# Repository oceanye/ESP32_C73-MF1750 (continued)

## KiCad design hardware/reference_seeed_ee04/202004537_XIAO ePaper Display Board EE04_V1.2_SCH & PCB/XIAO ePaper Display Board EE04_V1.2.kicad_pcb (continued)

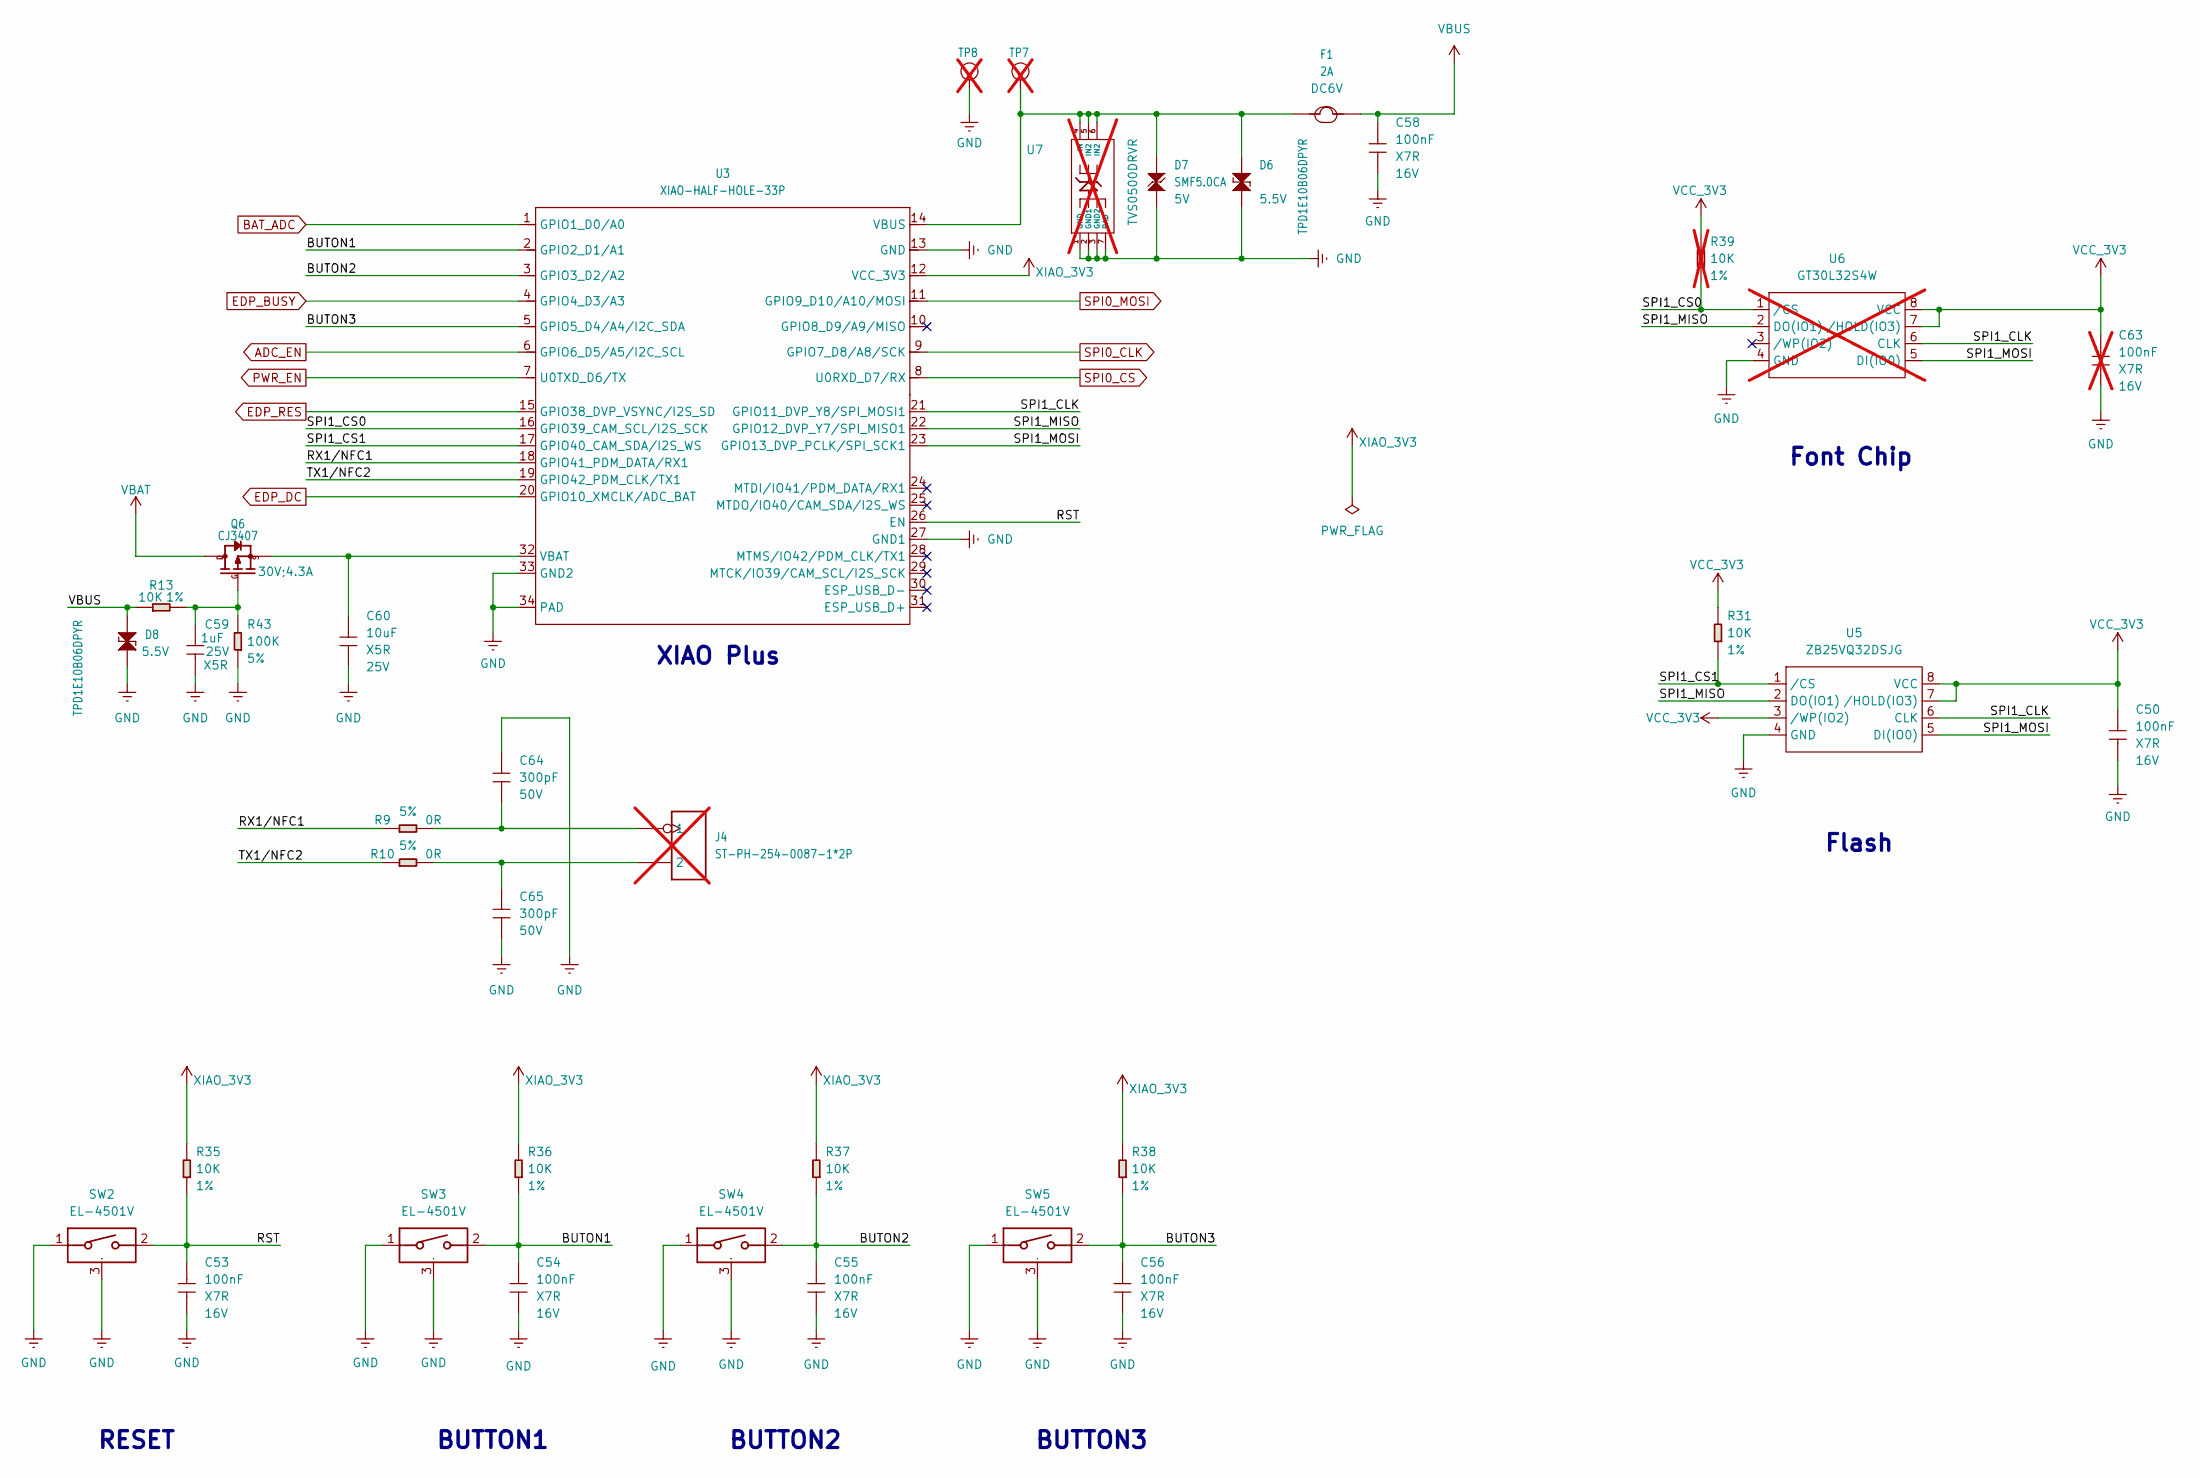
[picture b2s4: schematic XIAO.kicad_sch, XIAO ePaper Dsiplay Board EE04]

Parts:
C50, C53, C54, C55, C56, C58: 100nF; C0402; Voltage Rating 16V; MPN CC0402KRX7R7BB104
C59: 1uF; C0402; Voltage Rating 25V; MPN CC0402KRX5R8BB105
C60: 10uF; C0805; Voltage Rating 25V; MPN CC0805KKX5R8BB106
C63: 100nF; C0402; Voltage Rating 16V; MPN CC0402KRX7R7BB104; not fitted
C64, C65: 300pF; C0402; Voltage Rating 50V; MPN GRM1555C1H301JA01D
D6, D8: TPD1E10B06DPYR; ESD-0402; Rating 5.5V; MPN TPD1E10B06DPYR
D7: SMF5.0CA; SOD-123; Rating 5V; MPN SMF5.0CA
F1: 2A; F1210; Rating DC6V; MPN SMD1210R200SF
J4: ST-PH-254-0087-1*2P; H2P-2.54-65_40MIL; MPN ST-PH-254-0087-1*2P; not fitted
Q6: CJ3407; SOT23; Rating 30V;4.3A; MPN CJ3407
R9, R10: 0R; R0402; Power Rating 5%; MPN RC0402JR-070RL
R13, R31, R35, R36, R37, R38: 10K; R0402; Power Rating 1%; MPN RC0402FR-0710KL
R39: 10K; R0402; Power Rating 1%; MPN RC0402FR-0710KL; not fitted
R43: 100K; R0402; Power Rating 5%; MPN RC0402JR-07100KL
SW2, SW3, SW4, SW5: EL-4501V; SW3-DIP-SIDE-4.5X4.5X5.5MM; MPN EL-4501V
TP7, TP8: Test Point; TP-D45MIL; Part Type Test Point; not fitted
U3: XIAO-HALF-HOLE-33P; XIAO-ESP32-S3-Plus-SMD
U5: ZB25VQ32DSJG; SOIC8-1.27-5.3X5.3MM; MPN ZB25VQ32DSJG
U6: GT30L32S4W; SOP8-1.27-5.2X5.2x2.16MM; MPN GT30L32S4W; not fitted
U7: TVS0500DRVR; WSON7-0.65-2X2X0.8MM; MPN TVS0500DRVR; not fitted

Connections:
/XIAO/BUTON1: C54.1, R36.1, SW3.2, U3.2 (GPIO2_D1/A1)
/XIAO/BUTON2: C55.1, R37.1, SW4.2, U3.3 (GPIO3_D2/A2)
/XIAO/BUTON3: C56.1, R38.1, SW5.2, U3.5 (GPIO5_D4/A4/I2C_SDA)
/XIAO/RST: C53.1, R35.1, SW2.2, U3.26 (EN)
/XIAO/RX1/NFC1: R9.1, U3.18 (GPIO41_PDM_DATA/RX1)
/XIAO/SPI1_CLK: U3.21 (GPIO11_DVP_Y8/SPI_MOSI1), U5.6 (CLK), U6.6 (CLK)
/XIAO/SPI1_CS0: R39.1, U3.16 (GPIO39_CAM_SCL/I2S_SCK), U6.1 (/CS)
/XIAO/SPI1_CS1: R31.1, U3.17 (GPIO40_CAM_SDA/I2S_WS), U5.1 (/CS)
/XIAO/SPI1_MISO: U3.22 (GPIO12_DVP_Y7/SPI_MISO1), U5.2 (DO(IO1)), U6.2 (DO(IO1))
/XIAO/SPI1_MOSI: U3.23 (GPIO13_DVP_PCLK/SPI_SCK1), U5.5 (DI(IO0)), U6.5 (DI(IO0))
/XIAO/TX1/NFC2: R10.1, U3.19 (GPIO42_PDM_CLK/TX1)
ADC_EN: U3.6 (GPIO6_D5/A5/I2C_SCL); also elsewhere on the board
BAT_ADC: U3.1 (GPIO1_D0/A0); also elsewhere on the board
EDP_BUSY: U3.4 (GPIO4_D3/A3); also elsewhere on the board
EDP_DC: U3.20 (GPIO10_XMCLK/ADC_BAT); also elsewhere on the board
EDP_RES: U3.15 (GPIO38_DVP_VSYNC/I2S_SD); also elsewhere on the board
GND: C50.2, C53.2, C54.2, C55.2, C56.2, C58.2, C59.2, C60.1, C63.2, C64.1, C65.2, D6.1, D7.1, D8.1, R43.1, SW2.1, SW2.3 (GND), SW3.1, SW3.3 (GND), SW4.1, SW4.3 (GND), SW5.1, SW5.3 (GND), TP8.1 (T), U3.13 (GND), U3.27 (GND1), U3.33 (GND2), U3.34 (PAD), U5.4 (GND), U6.4 (GND), U7.1 (GND), U7.2 (GND1), U7.3 (GND2), U7.7 (PAD); also elsewhere on the board
unnamed: C64.2, J4.1, R9.2
unnamed: C65.1, J4.2, R10.2
unnamed: C59.1, Q6.1 (G), R13.2, R43.2
unnamed: C60.2, Q6.2 (S), U3.32 (VBAT)
unnamed: D6.2, D7.2, F1.1, TP7.1 (T), U3.14 (VBUS), U7.4 (IN), U7.5 (IN2), U7.6 (IN2)
PWR_EN: U3.7 (U0TXD_D6/TX); also elsewhere on the board
SPI0_CLK: U3.9 (GPIO7_D8/A8/SCK); also elsewhere on the board
SPI0_CS: U3.8 (U0RXD_D7/RX); also elsewhere on the board
SPI0_MOSI: U3.11 (GPIO9_D10/A10/MOSI); also elsewhere on the board
VBAT: Q6.3 (D); also elsewhere on the board
VBUS: C58.1, D8.2, F1.2, R13.1; also elsewhere on the board
VCC_3V3: C50.1, C63.1, R31.2, R39.2, U5.3 (/WP(IO2)), U5.7 (/HOLD(IO3)), U5.8 (VCC), U6.7 (/HOLD(IO3)), U6.8 (VCC); also elsewhere on the board
XIAO_3V3: R35.2, R36.2, R37.2, R38.2, U3.12 (VCC_3V3)

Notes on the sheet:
BUTTON1
BUTTON2
Flash
BUTTON3
Font Chip
RESET
XIAO Plus

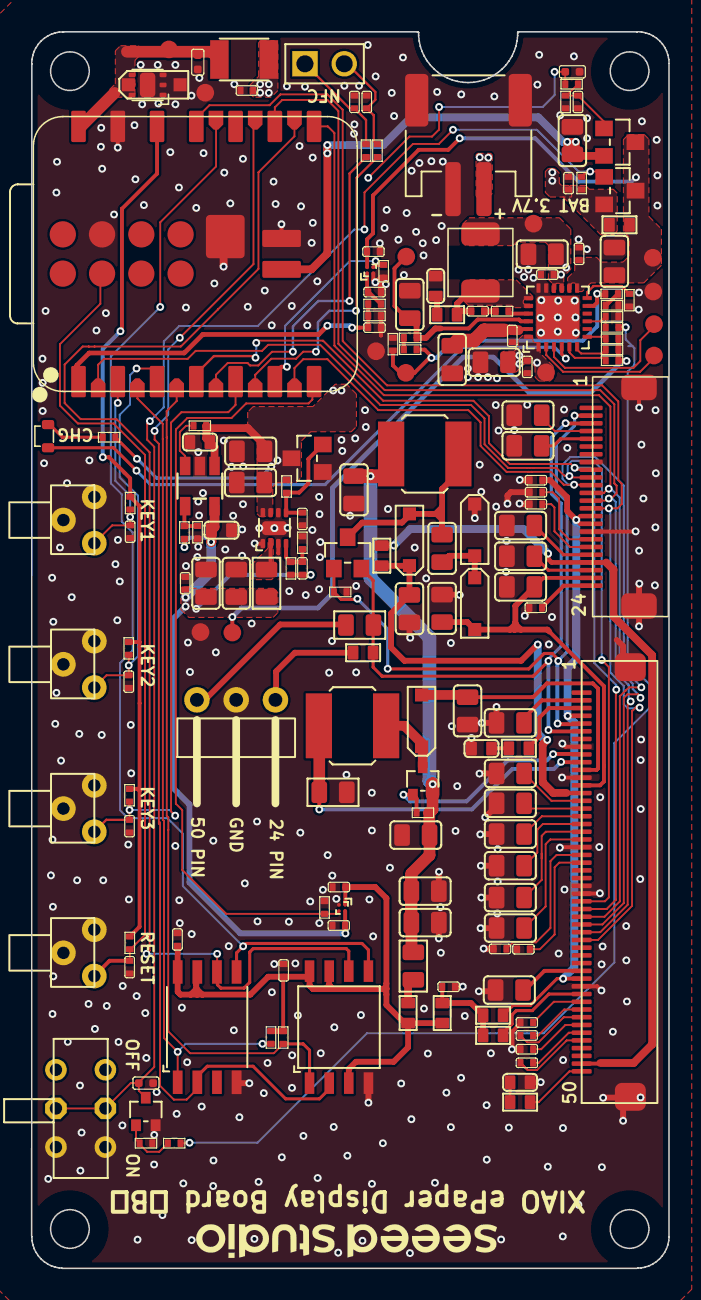
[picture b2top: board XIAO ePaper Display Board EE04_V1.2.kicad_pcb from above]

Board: 2 copper layers, 41.2 x 80.0 mm, 174 parts (0 on the bottom side), 104 nets.
